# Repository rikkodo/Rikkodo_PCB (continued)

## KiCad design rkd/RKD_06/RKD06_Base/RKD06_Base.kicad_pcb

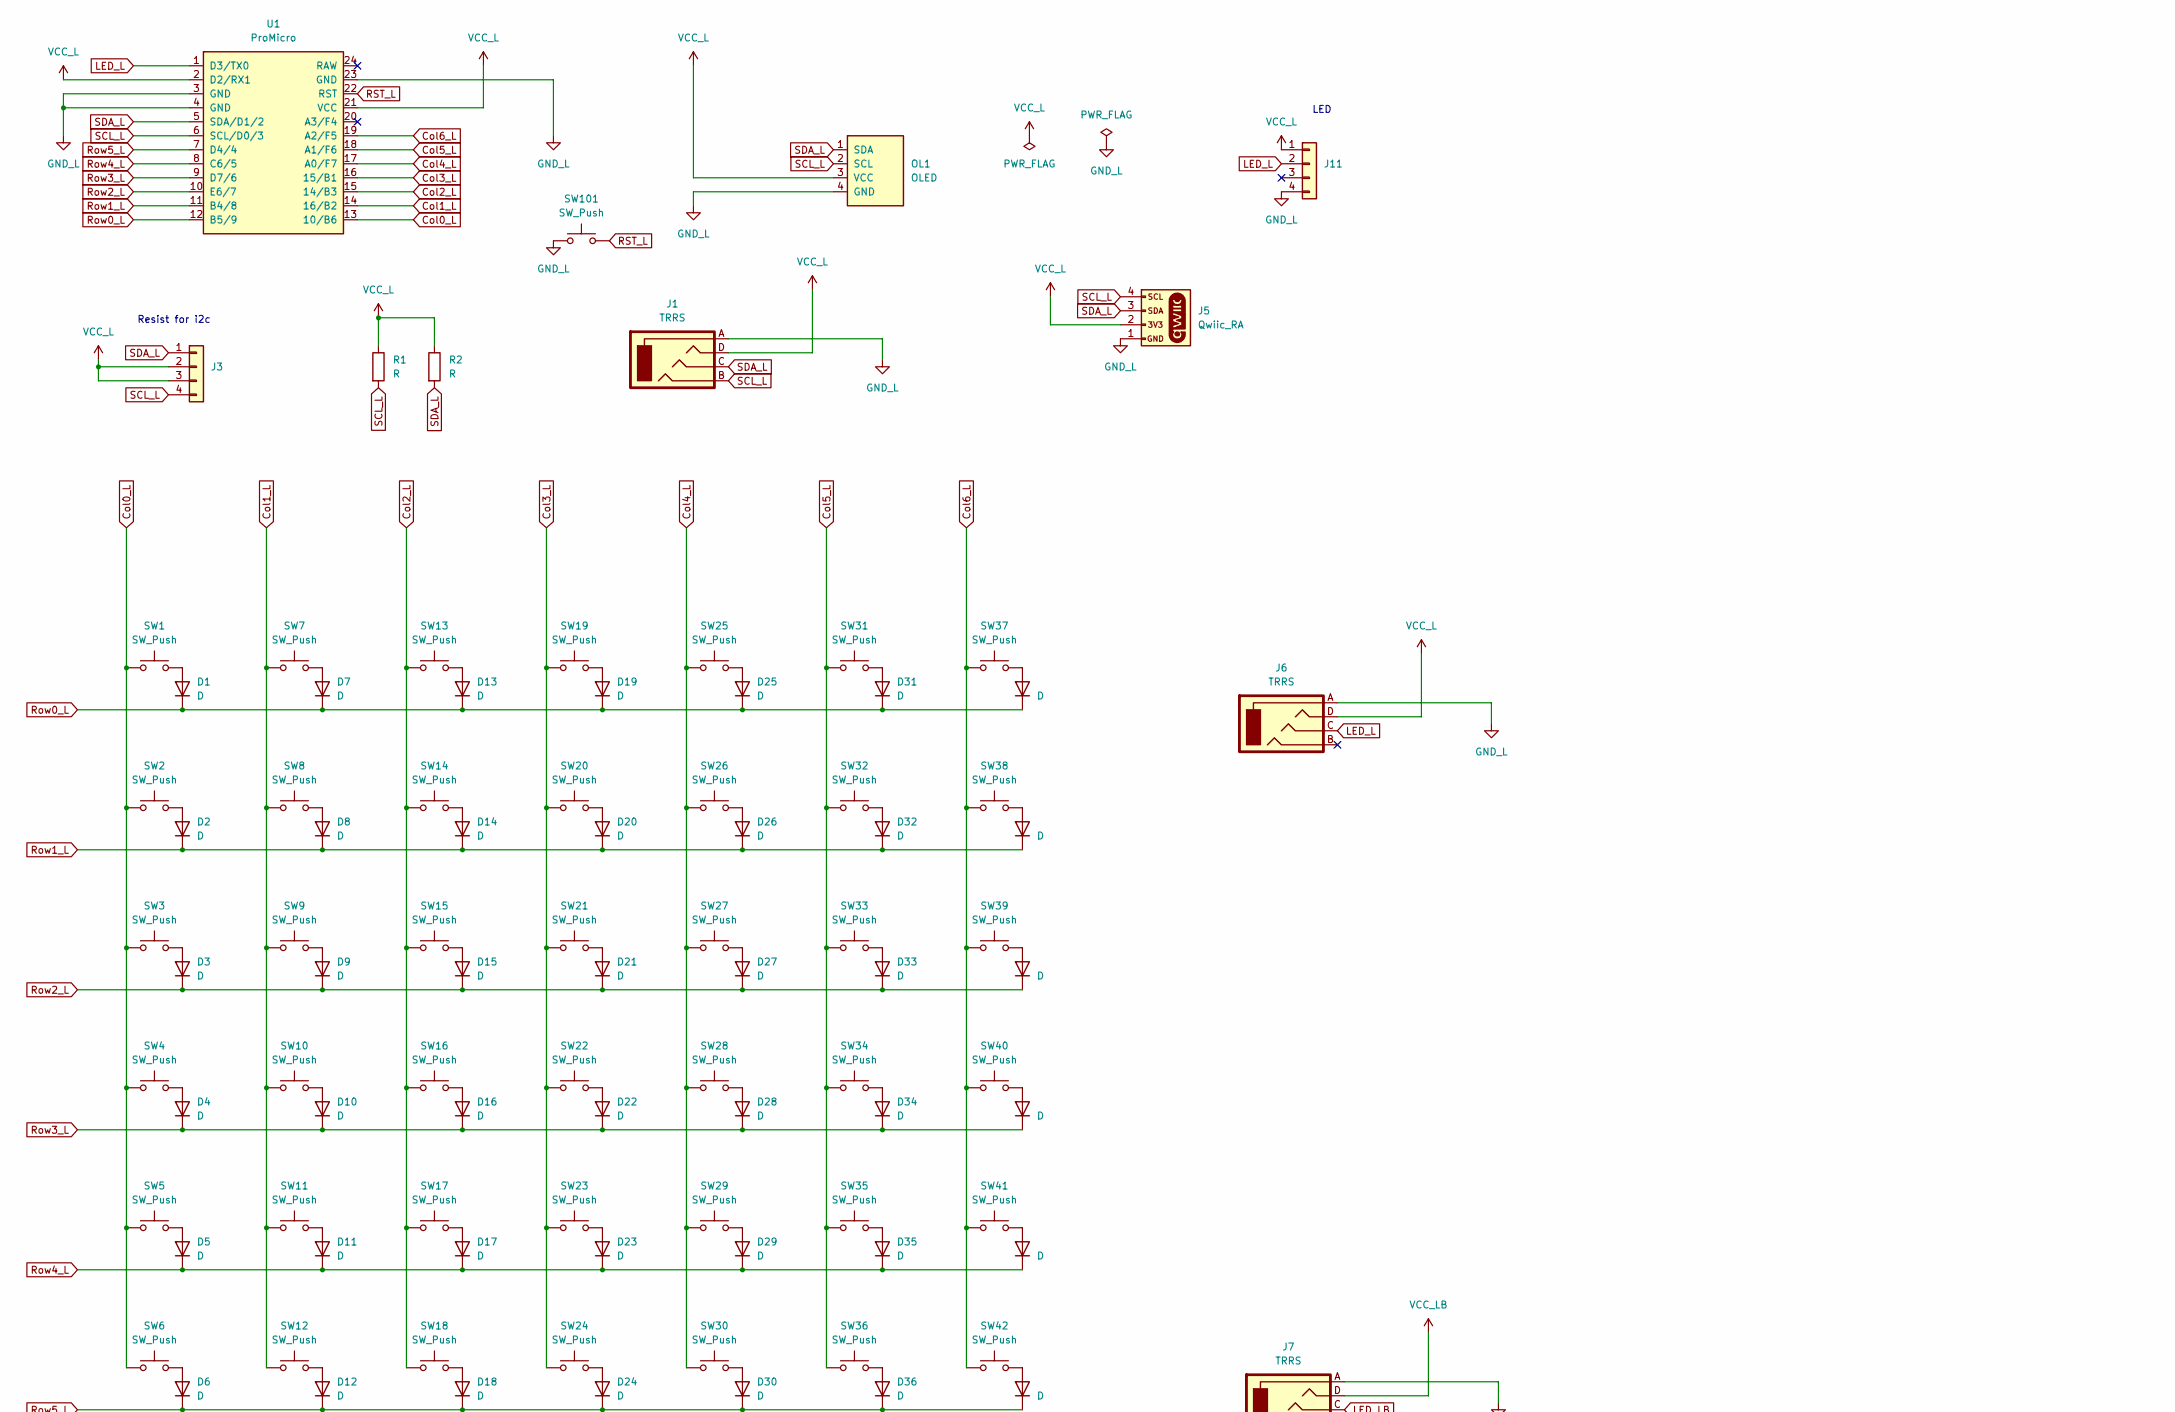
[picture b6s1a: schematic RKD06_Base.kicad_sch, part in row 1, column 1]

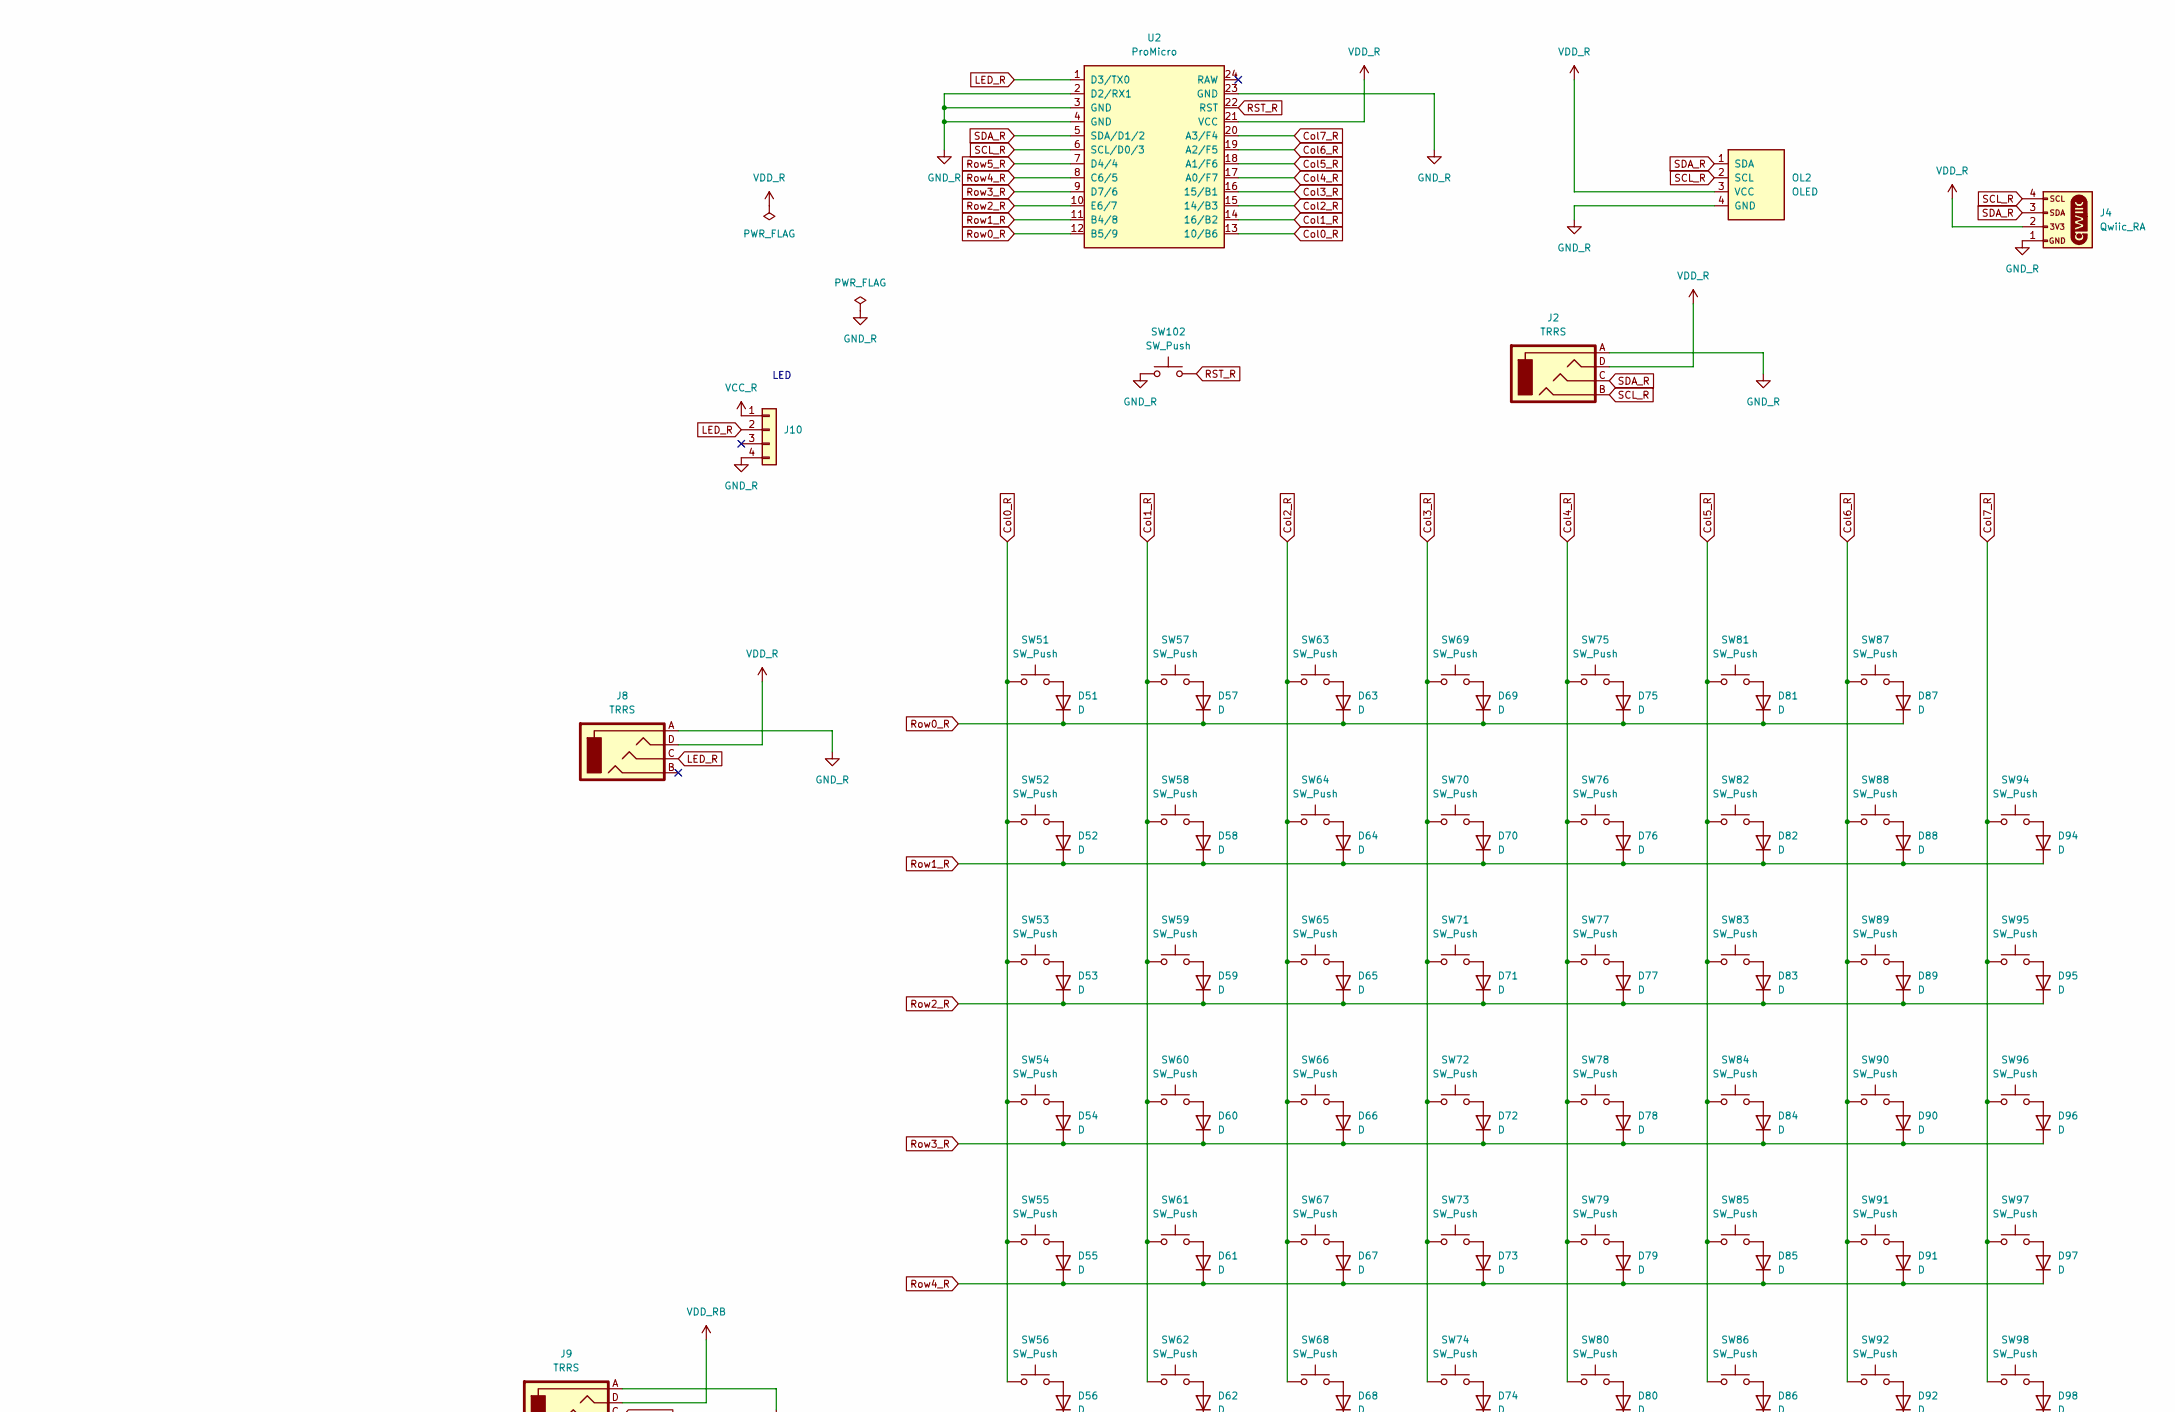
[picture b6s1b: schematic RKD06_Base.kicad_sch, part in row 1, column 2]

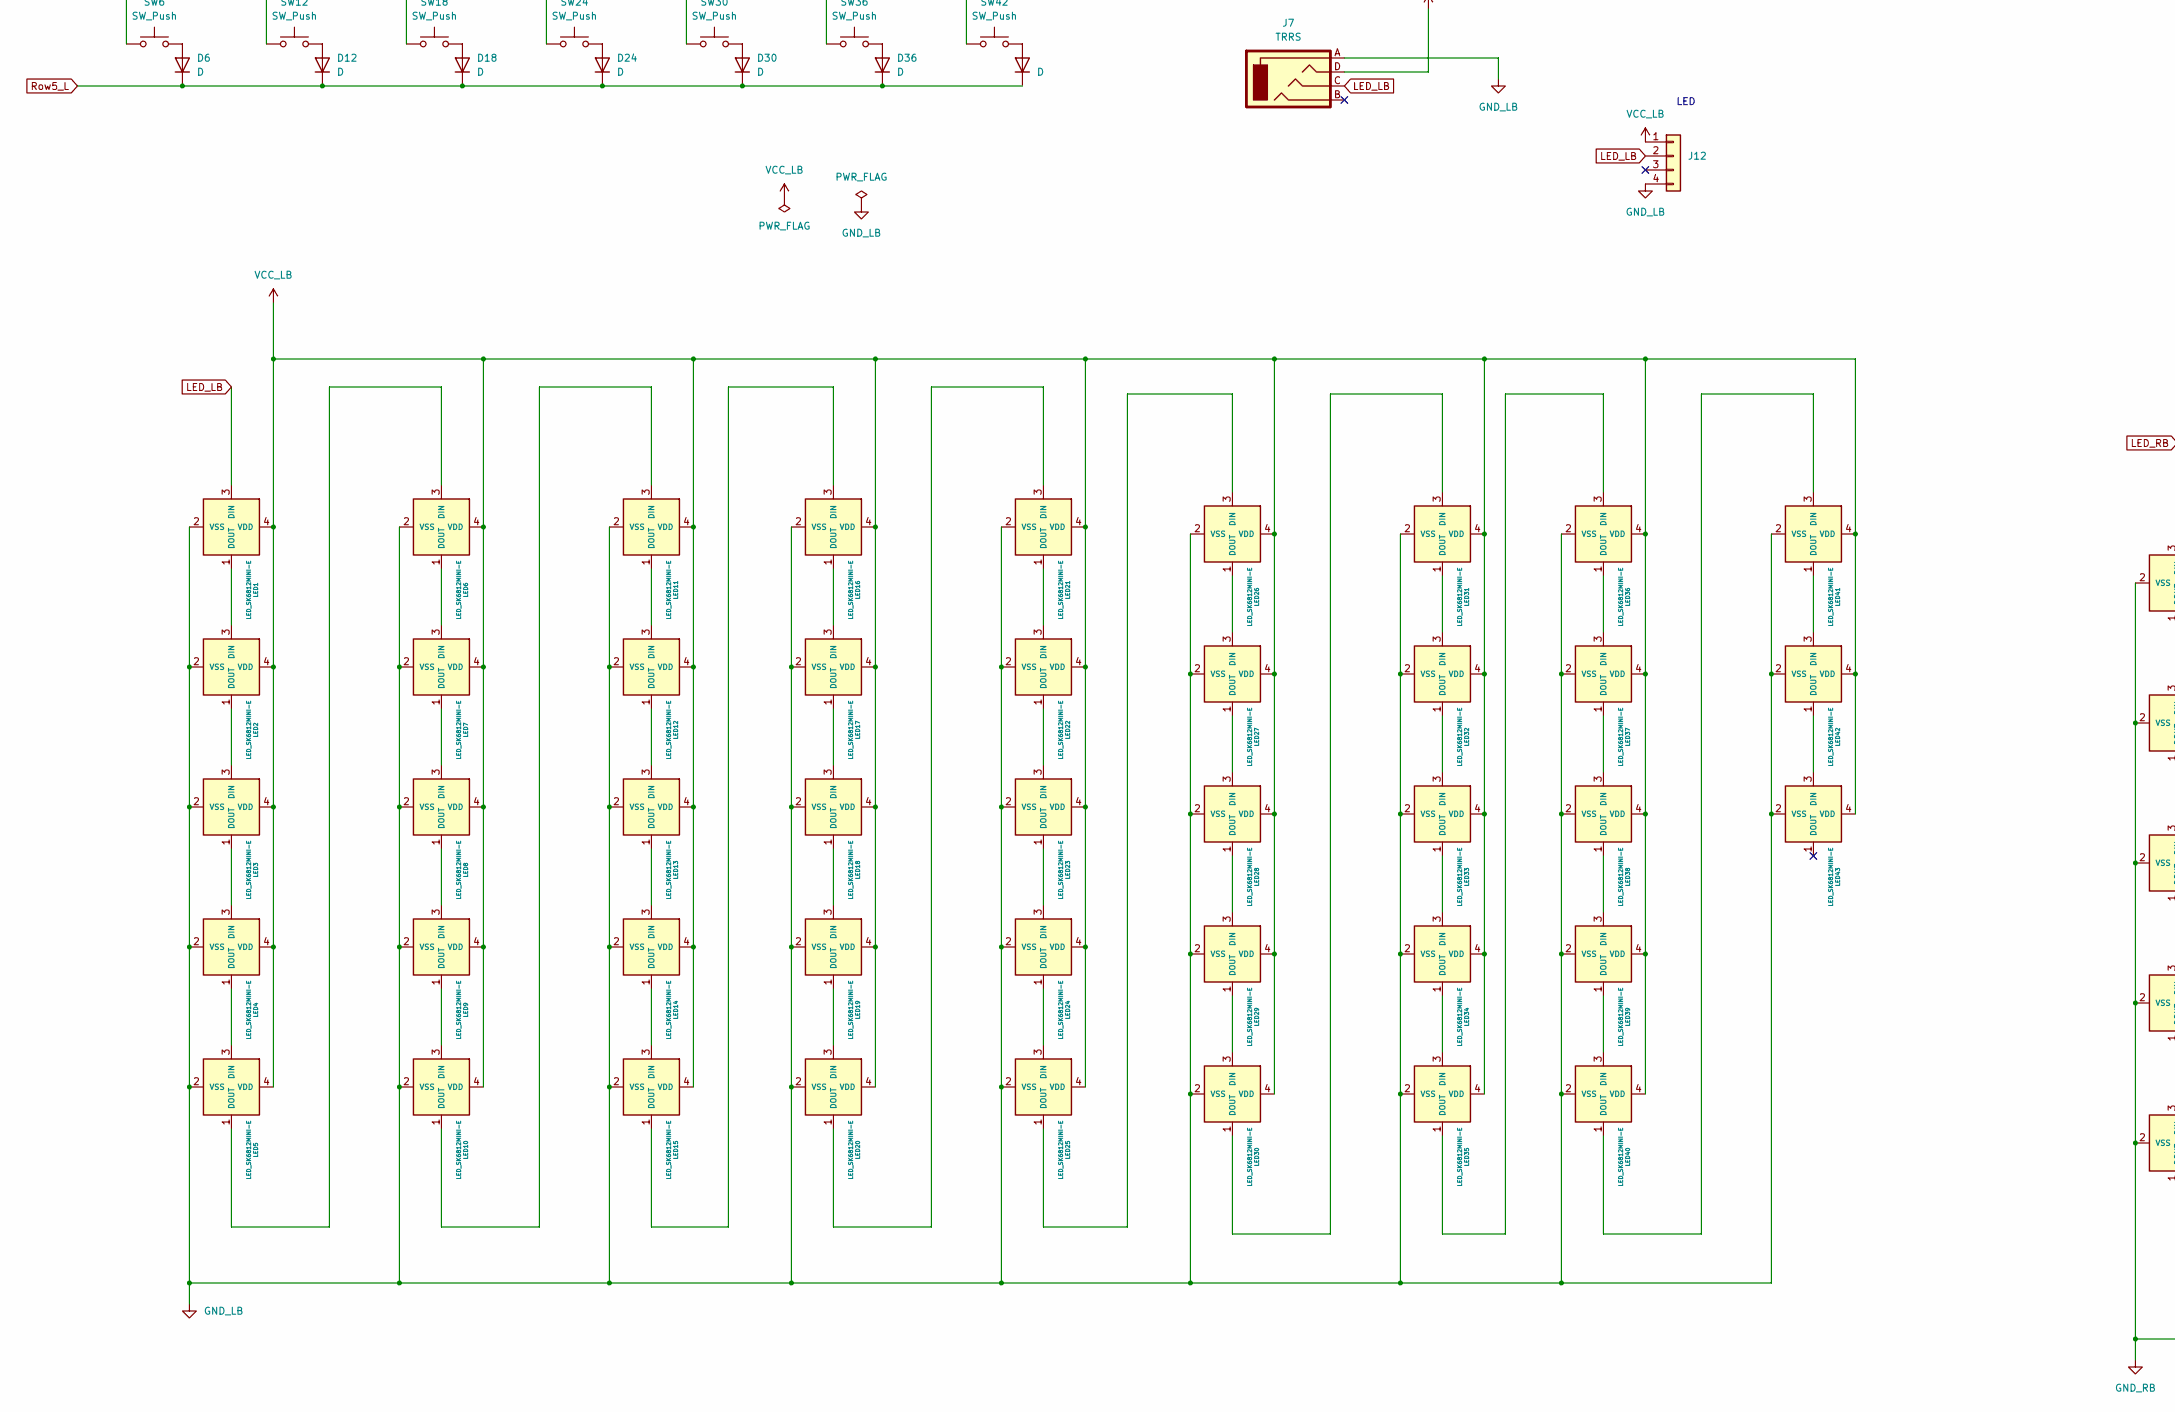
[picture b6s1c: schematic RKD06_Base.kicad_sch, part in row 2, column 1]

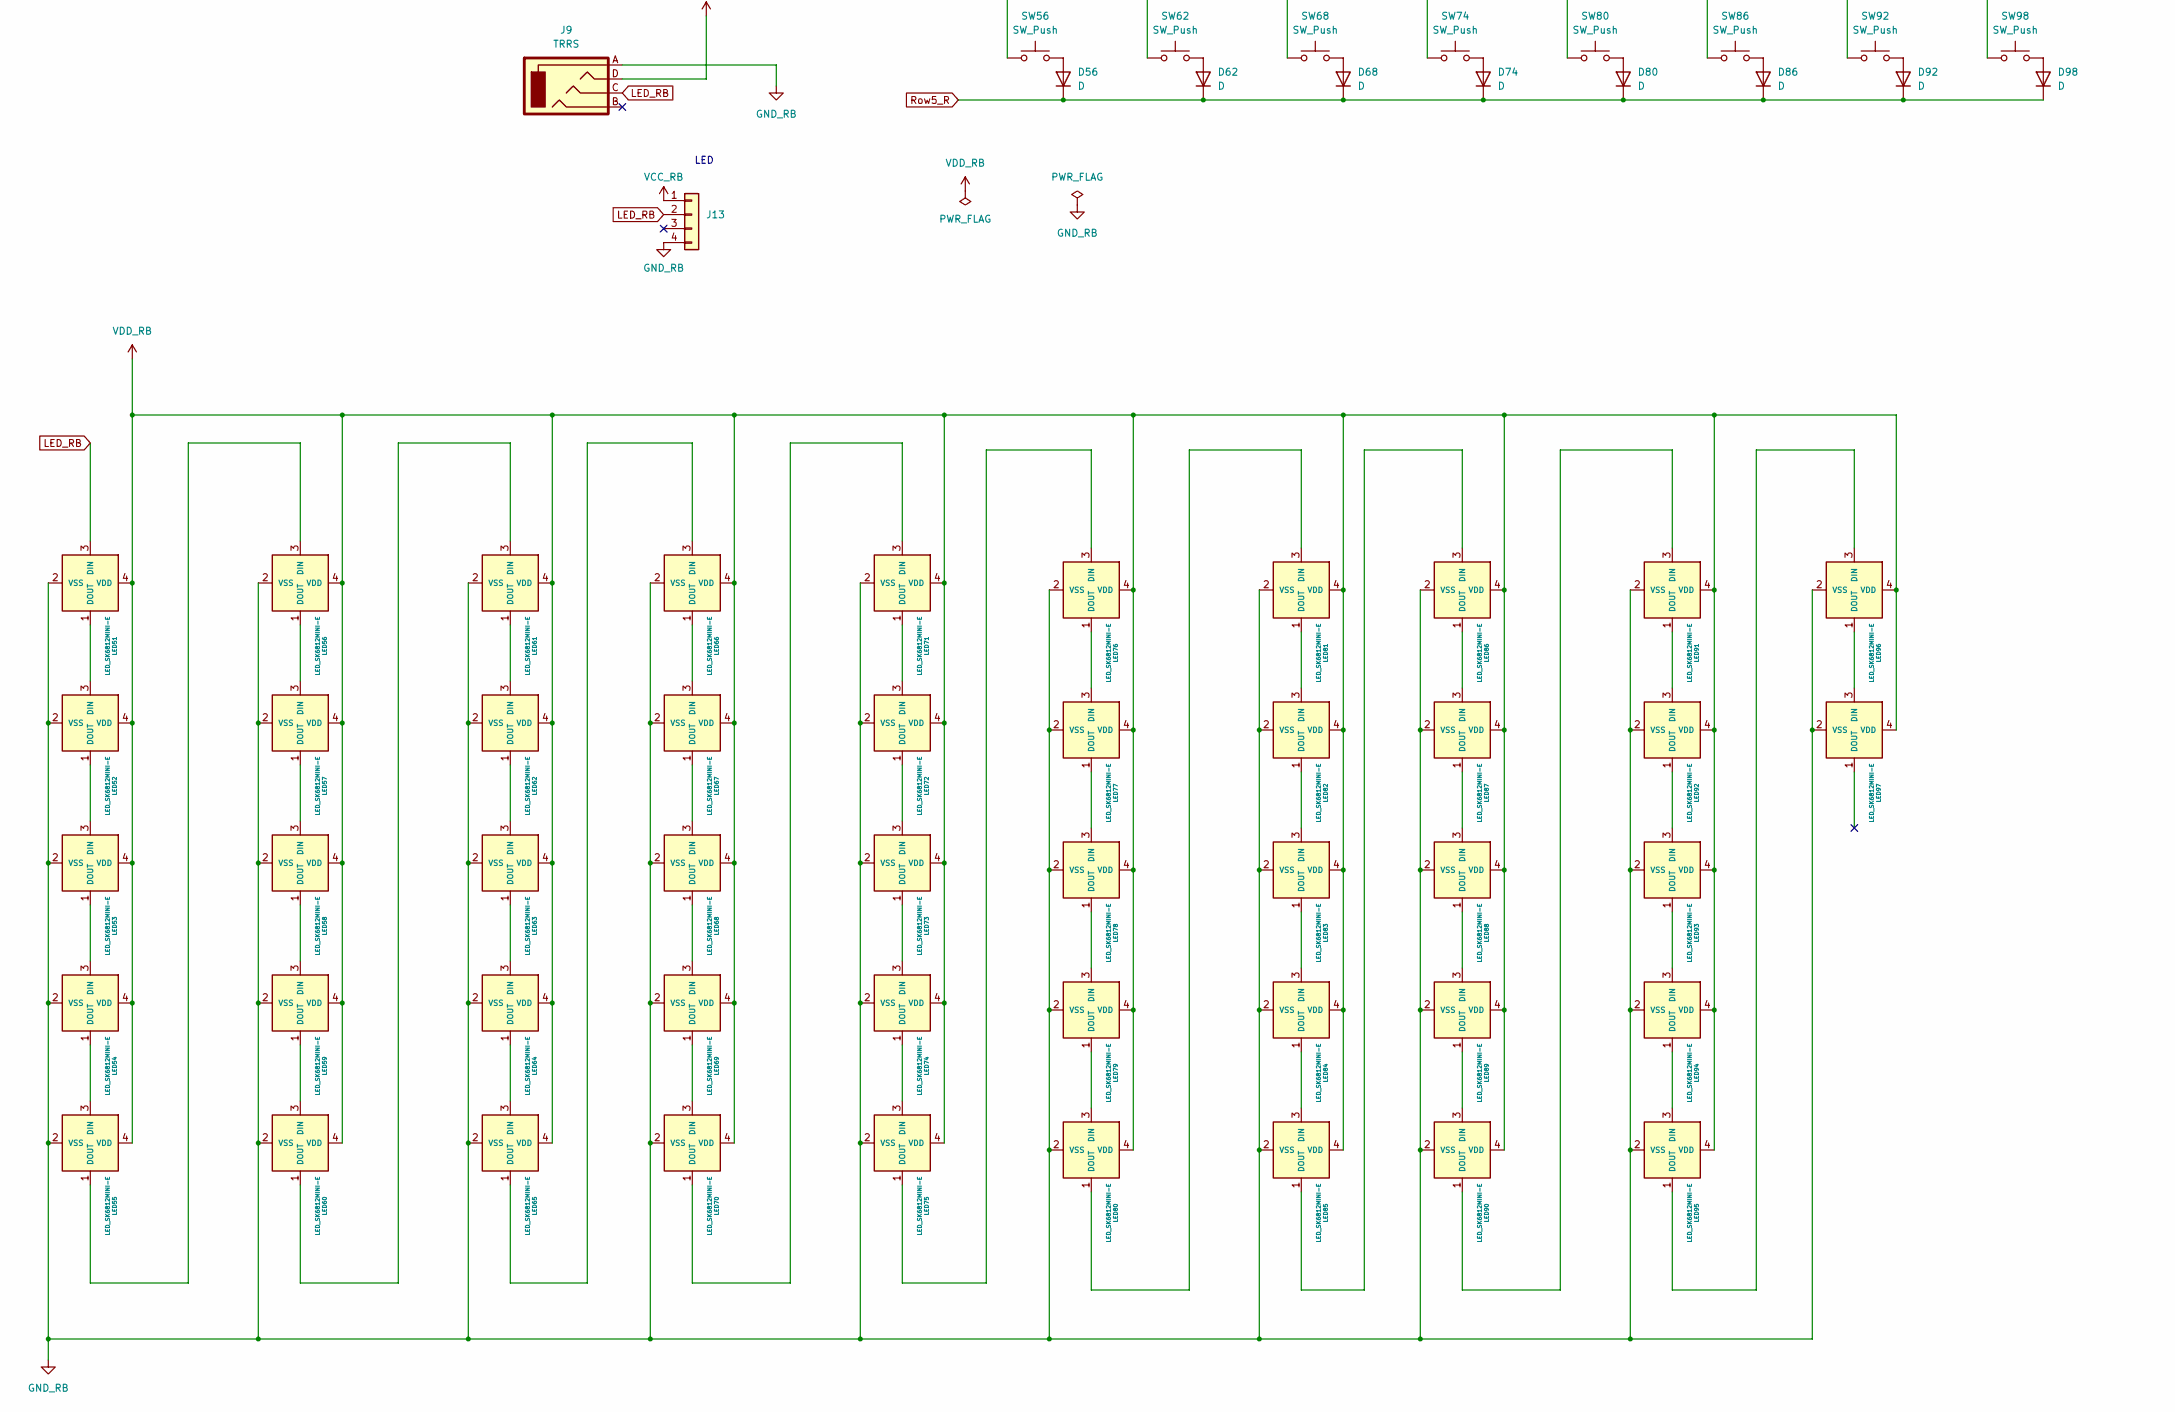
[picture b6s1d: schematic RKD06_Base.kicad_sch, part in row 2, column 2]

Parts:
D1, D2, D3, D4, D5, D6, D7, D8, D9, D10, D11, D12, D13, D14, D15, D16, D17, D18, D19, D20, D21, D22, D23, D24, D25, D26, D27, D28, D29, D30, D31, D32, D33, D34, D35, D36, D37, D38, D39, D40, D41, D42, D51, D52, D53, D54, D55, D56, D57, D58, D59, D60, D61, D62, D63, D64, D65, D66, D67, D68, D69, D70, D71, D72, D73, D74, D75, D76, D77, D78, D79, D80, D81, D82, D83, D84, D85, D86, D87, D88, D89, D90, D91, D92, D94, D95, D96, D97, D98: D; Diode_SMD
J1, J2, J6, J7, J8, J9: TRRS; TRRS_PJ-320A
J3, J10, J11: Conn_01x04; PinSocket_1x04_P2.54mm_Horizontal
J4, J5: Qwiic_RA; JST_SMD_1.0mm-4_Black
J12, J13: Conn_01x04; PinHeader_1x04_P2.54mm_Horizontal
LED1, LED2, LED3, LED4, LED5, LED6, LED7, LED8, LED9, LED10, LED11, LED12, LED13, LED14, LED15, LED16, LED17, LED18, LED19, LED20, LED21, LED22, LED23, LED24, LED25, LED26, LED27, LED28, LED29, LED30, LED31, LED32, LED33, LED34, LED35, LED36, LED37, LED38, LED39, LED40, LED41, LED42, LED43, LED51, LED52, LED53, LED54, LED55, LED56, LED57, LED58, LED59, LED60, LED61, LED62, LED63, LED64, LED65, LED66, LED67, LED68, LED69, LED70, LED71, LED72, LED73, LED74, LED75, LED76, LED77, LED78, LED79, LED80, LED81, LED82, LED83, LED84, LED85, LED86, LED87, LED88, LED89, LED90, LED91, LED92, LED93, LED94, LED95, LED96, LED97: LED_SK6812MINI-E; LED_SK6812MINI-E_BL
OL1, OL2: OLED; OLED_center_module
R1, R2: R; R_Axial_DIN0207_L6.3mm_D2.5mm_P10.16mm_Horizontal
SW1, SW2, SW3, SW4, SW5, SW6, SW7, SW8, SW9, SW10, SW12, SW13, SW14, SW15, SW16, SW17, SW18, SW19, SW20, SW21, SW22, SW23, SW24, SW25, SW26, SW27, SW28, SW29, SW30, SW31, SW32, SW33, SW34, SW35, SW37, SW38, SW39, SW40, SW41, SW42, SW51, SW52, SW53, SW54, SW55, SW56, SW57, SW58, SW59, SW60, SW61, SW62, SW63, SW64, SW65, SW66, SW67, SW68, SW69, SW70, SW71, SW72, SW73, SW74, SW75, SW76, SW77, SW78, SW79, SW80, SW81, SW82, SW83, SW84, SW85, SW86, SW87, SW88, SW89, SW90, SW91, SW92, SW95, SW97, SW98: SW_Push; rkd_Asm_ChocV1V2_Hotswap_1u
SW11, SW36, SW94, SW96: SW_Push; rkd_Asm_ChocV1V2byV1_Hotswap_2u
SW101, SW102: SW_Push; ResetSW
U1, U2: ProMicro; ProMicro_r

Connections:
Col0_L: SW1.2, SW2.2, SW3.2, SW4.2, SW5.2, SW6.2, U1.13 (10/B6)
Col0_R: SW51.2, SW52.2, SW53.2, SW54.2, SW55.2, SW56.2, U2.13 (10/B6)
Col1_L: SW7.2, SW8.2, SW9.2, SW10.2, SW11.2, SW12.2, U1.14 (16/B2)
Col1_R: SW57.2, SW58.2, SW59.2, SW60.2, SW61.2, SW62.2, U2.14 (16/B2)
Col2_L: SW13.2, SW14.2, SW15.2, SW16.2, SW17.2, SW18.2, U1.15 (14/B3)
Col2_R: SW63.2, SW64.2, SW65.2, SW66.2, SW67.2, SW68.2, U2.15 (14/B3)
Col3_L: SW19.2, SW20.2, SW21.2, SW22.2, SW23.2, SW24.2, U1.16 (15/B1)
Col3_R: SW69.2, SW70.2, SW71.2, SW72.2, SW73.2, SW74.2, U2.16 (15/B1)
Col4_L: SW25.2, SW26.2, SW27.2, SW28.2, SW29.2, SW30.2, U1.17 (A0/F7)
Col4_R: SW75.2, SW76.2, SW77.2, SW78.2, SW79.2, SW80.2, U2.17 (A0/F7)
Col5_L: SW31.2, SW32.2, SW33.2, SW34.2, SW35.2, SW36.2, U1.18 (A1/F6)
Col5_R: SW81.2, SW82.2, SW83.2, SW84.2, SW85.2, SW86.2, U2.18 (A1/F6)
Col6_L: SW37.2, SW38.2, SW39.2, SW40.2, SW41.2, SW42.2, U1.19 (A2/F5)
Col6_R: SW87.2, SW88.2, SW89.2, SW90.2, SW91.2, SW92.2, U2.19 (A2/F5)
Col7_R: SW94.2, SW95.2, SW96.2, SW97.2, SW98.2, U2.20 (A3/F4)
GND_L: J1.A, J5.1, J6.A, J11.4, OL1.4 (GND), SW101.2, U1.3 (GND), U1.4 (GND), U1.23 (GND)
GND_LB: J7.A, J12.4, LED1.2 (VSS), LED2.2 (VSS), LED3.2 (VSS), LED4.2 (VSS), LED5.2 (VSS), LED6.2 (VSS), LED7.2 (VSS), LED8.2 (VSS), LED9.2 (VSS), LED10.2 (VSS), LED11.2 (VSS), LED12.2 (VSS), LED13.2 (VSS), LED14.2 (VSS), LED15.2 (VSS), LED16.2 (VSS), LED17.2 (VSS), LED18.2 (VSS), LED19.2 (VSS), LED20.2 (VSS), LED21.2 (VSS), LED22.2 (VSS), LED23.2 (VSS), LED24.2 (VSS), LED25.2 (VSS), LED26.2 (VSS), LED27.2 (VSS), LED28.2 (VSS), LED29.2 (VSS), LED30.2 (VSS), LED31.2 (VSS), LED32.2 (VSS), LED33.2 (VSS), LED34.2 (VSS), LED35.2 (VSS), LED36.2 (VSS), LED37.2 (VSS), LED38.2 (VSS), LED39.2 (VSS), LED40.2 (VSS), LED41.2 (VSS), LED42.2 (VSS), LED43.2 (VSS)
GND_R: J2.A, J4.1, J8.A, J10.4, OL2.4 (GND), SW102.2, U2.2 (D2/RX1), U2.3 (GND), U2.4 (GND), U2.23 (GND)
GND_RB: J9.A, J13.4, LED51.2 (VSS), LED52.2 (VSS), LED53.2 (VSS), LED54.2 (VSS), LED55.2 (VSS), LED56.2 (VSS), LED57.2 (VSS), LED58.2 (VSS), LED59.2 (VSS), LED60.2 (VSS), LED61.2 (VSS), LED62.2 (VSS), LED63.2 (VSS), LED64.2 (VSS), LED65.2 (VSS), LED66.2 (VSS), LED67.2 (VSS), LED68.2 (VSS), LED69.2 (VSS), LED70.2 (VSS), LED71.2 (VSS), LED72.2 (VSS), LED73.2 (VSS), LED74.2 (VSS), LED75.2 (VSS), LED76.2 (VSS), LED77.2 (VSS), LED78.2 (VSS), LED79.2 (VSS), LED80.2 (VSS), LED81.2 (VSS), LED82.2 (VSS), LED83.2 (VSS), LED84.2 (VSS), LED85.2 (VSS), LED86.2 (VSS), LED87.2 (VSS), LED88.2 (VSS), LED89.2 (VSS), LED90.2 (VSS), LED91.2 (VSS), LED92.2 (VSS), LED93.2 (VSS), LED94.2 (VSS), LED95.2 (VSS), LED96.2 (VSS), LED97.2 (VSS)
LED_L: J6.C, J11.2, U1.1 (D3/TX0)
LED_LB: J7.C, J12.2, LED1.3 (DIN)
LED_R: J8.C, J10.2, U2.1 (D3/TX0)
LED_RB: J9.C, J13.2, LED51.3 (DIN)
unnamed: D1.2 (A), SW1.1
unnamed: D2.2 (A), SW2.1
unnamed: D3.2 (A), SW3.1
unnamed: D4.2 (A), SW4.1
unnamed: D5.2 (A), SW5.1
unnamed: D6.2 (A), SW6.1
unnamed: D7.2 (A), SW7.1
unnamed: D8.2 (A), SW8.1
unnamed: D9.2 (A), SW9.1
unnamed: D10.2 (A), SW10.1
unnamed: D11.2 (A), SW11.1
unnamed: D12.2 (A), SW12.1
unnamed: D13.2 (A), SW13.1
unnamed: D14.2 (A), SW14.1
unnamed: D15.2 (A), SW15.1
unnamed: D16.2 (A), SW16.1
unnamed: D17.2 (A), SW17.1
unnamed: D18.2 (A), SW18.1
unnamed: D19.2 (A), SW19.1
unnamed: D20.2 (A), SW20.1
unnamed: D21.2 (A), SW21.1
unnamed: D22.2 (A), SW22.1
unnamed: D23.2 (A), SW23.1
unnamed: D24.2 (A), SW24.1
unnamed: D25.2 (A), SW25.1
unnamed: D26.2 (A), SW26.1
unnamed: D27.2 (A), SW27.1
unnamed: D28.2 (A), SW28.1
unnamed: D29.2 (A), SW29.1
unnamed: D30.2 (A), SW30.1
unnamed: D31.2 (A), SW31.1
unnamed: D32.2 (A), SW32.1
unnamed: D33.2 (A), SW33.1
unnamed: D34.2 (A), SW34.1
unnamed: D35.2 (A), SW35.1
unnamed: D36.2 (A), SW36.1
unnamed: D37.2 (A), SW37.1
unnamed: D38.2 (A), SW38.1
unnamed: D39.2 (A), SW39.1
unnamed: D40.2 (A), SW40.1
unnamed: D41.2 (A), SW41.1
unnamed: D42.2 (A), SW42.1
unnamed: D51.2 (A), SW51.1
unnamed: D52.2 (A), SW52.1
unnamed: D53.2 (A), SW53.1
unnamed: D54.2 (A), SW54.1
unnamed: D55.2 (A), SW55.1
unnamed: D56.2 (A), SW56.1
unnamed: D57.2 (A), SW57.1
unnamed: D58.2 (A), SW58.1
unnamed: D59.2 (A), SW59.1
unnamed: D60.2 (A), SW60.1
unnamed: D61.2 (A), SW61.1
unnamed: D62.2 (A), SW62.1
unnamed: D63.2 (A), SW63.1
unnamed: D64.2 (A), SW64.1
unnamed: D65.2 (A), SW65.1
unnamed: D66.2 (A), SW66.1
unnamed: D67.2 (A), SW67.1
unnamed: D68.2 (A), SW68.1
unnamed: D69.2 (A), SW69.1
unnamed: D70.2 (A), SW70.1
unnamed: D71.2 (A), SW71.1
unnamed: D72.2 (A), SW72.1
unnamed: D73.2 (A), SW73.1
unnamed: D74.2 (A), SW74.1
unnamed: D75.2 (A), SW75.1
unnamed: D76.2 (A), SW76.1
unnamed: D77.2 (A), SW77.1
unnamed: D78.2 (A), SW78.1
unnamed: D79.2 (A), SW79.1
unnamed: D80.2 (A), SW80.1
unnamed: D81.2 (A), SW81.1
unnamed: D82.2 (A), SW82.1
unnamed: D83.2 (A), SW83.1
unnamed: D84.2 (A), SW84.1
unnamed: D85.2 (A), SW85.1
unnamed: D86.2 (A), SW86.1
unnamed: D87.2 (A), SW87.1
unnamed: D88.2 (A), SW88.1
unnamed: D89.2 (A), SW89.1
unnamed: D90.2 (A), SW90.1
unnamed: D91.2 (A), SW91.1
unnamed: D92.2 (A), SW92.1
unnamed: D94.2 (A), SW94.1
unnamed: D95.2 (A), SW95.1
unnamed: D96.2 (A), SW96.1
unnamed: D97.2 (A), SW97.1
unnamed: D98.2 (A), SW98.1
unnamed: LED1.1 (DOUT), LED2.3 (DIN)
unnamed: LED2.1 (DOUT), LED3.3 (DIN)
unnamed: LED3.1 (DOUT), LED4.3 (DIN)
unnamed: LED4.1 (DOUT), LED5.3 (DIN)
unnamed: LED5.1 (DOUT), LED6.3 (DIN)
unnamed: LED6.1 (DOUT), LED7.3 (DIN)
unnamed: LED7.1 (DOUT), LED8.3 (DIN)
unnamed: LED8.1 (DOUT), LED9.3 (DIN)
unnamed: LED9.1 (DOUT), LED10.3 (DIN)
unnamed: LED10.1 (DOUT), LED11.3 (DIN)
unnamed: LED11.1 (DOUT), LED12.3 (DIN)
unnamed: LED12.1 (DOUT), LED13.3 (DIN)
unnamed: LED13.1 (DOUT), LED14.3 (DIN)
unnamed: LED14.1 (DOUT), LED15.3 (DIN)
unnamed: LED15.1 (DOUT), LED16.3 (DIN)
unnamed: LED16.1 (DOUT), LED17.3 (DIN)
unnamed: LED17.1 (DOUT), LED18.3 (DIN)
unnamed: LED18.1 (DOUT), LED19.3 (DIN)
unnamed: LED19.1 (DOUT), LED20.3 (DIN)
unnamed: LED20.1 (DOUT), LED21.3 (DIN)
unnamed: LED21.1 (DOUT), LED22.3 (DIN)
unnamed: LED22.1 (DOUT), LED23.3 (DIN)
unnamed: LED23.1 (DOUT), LED24.3 (DIN)
unnamed: LED24.1 (DOUT), LED25.3 (DIN)
unnamed: LED25.1 (DOUT), LED26.3 (DIN)
unnamed: LED26.1 (DOUT), LED27.3 (DIN)
unnamed: LED27.1 (DOUT), LED28.3 (DIN)
unnamed: LED28.1 (DOUT), LED29.3 (DIN)
unnamed: LED29.1 (DOUT), LED30.3 (DIN)
unnamed: LED30.1 (DOUT), LED31.3 (DIN)
unnamed: LED31.1 (DOUT), LED32.3 (DIN)
unnamed: LED32.1 (DOUT), LED33.3 (DIN)
unnamed: LED33.1 (DOUT), LED34.3 (DIN)
unnamed: LED34.1 (DOUT), LED35.3 (DIN)
unnamed: LED35.1 (DOUT), LED36.3 (DIN)
unnamed: LED36.1 (DOUT), LED37.3 (DIN)
unnamed: LED37.1 (DOUT), LED38.3 (DIN)
unnamed: LED38.1 (DOUT), LED39.3 (DIN)
unnamed: LED39.1 (DOUT), LED40.3 (DIN)
unnamed: LED40.1 (DOUT), LED41.3 (DIN)
unnamed: LED41.1 (DOUT), LED42.3 (DIN)
unnamed: LED42.1 (DOUT), LED43.3 (DIN)
unnamed: LED51.1 (DOUT), LED52.3 (DIN)
unnamed: LED52.1 (DOUT), LED53.3 (DIN)
unnamed: LED53.1 (DOUT), LED54.3 (DIN)
unnamed: LED54.1 (DOUT), LED55.3 (DIN)
unnamed: LED55.1 (DOUT), LED56.3 (DIN)
unnamed: LED56.1 (DOUT), LED57.3 (DIN)
unnamed: LED57.1 (DOUT), LED58.3 (DIN)
unnamed: LED58.1 (DOUT), LED59.3 (DIN)
unnamed: LED59.1 (DOUT), LED60.3 (DIN)
unnamed: LED60.1 (DOUT), LED61.3 (DIN)
unnamed: LED61.1 (DOUT), LED62.3 (DIN)
unnamed: LED62.1 (DOUT), LED63.3 (DIN)
unnamed: LED63.1 (DOUT), LED64.3 (DIN)
unnamed: LED64.1 (DOUT), LED65.3 (DIN)
unnamed: LED65.1 (DOUT), LED66.3 (DIN)
unnamed: LED66.1 (DOUT), LED67.3 (DIN)
unnamed: LED67.1 (DOUT), LED68.3 (DIN)
unnamed: LED68.1 (DOUT), LED69.3 (DIN)
unnamed: LED69.1 (DOUT), LED70.3 (DIN)
unnamed: LED70.1 (DOUT), LED71.3 (DIN)
unnamed: LED71.1 (DOUT), LED72.3 (DIN)
unnamed: LED72.1 (DOUT), LED73.3 (DIN)
unnamed: LED73.1 (DOUT), LED74.3 (DIN)
unnamed: LED74.1 (DOUT), LED75.3 (DIN)
unnamed: LED75.1 (DOUT), LED76.3 (DIN)
unnamed: LED76.1 (DOUT), LED77.3 (DIN)
unnamed: LED77.1 (DOUT), LED78.3 (DIN)
unnamed: LED78.1 (DOUT), LED79.3 (DIN)
unnamed: LED79.1 (DOUT), LED80.3 (DIN)
unnamed: LED80.1 (DOUT), LED81.3 (DIN)
unnamed: LED81.1 (DOUT), LED82.3 (DIN)
unnamed: LED82.1 (DOUT), LED83.3 (DIN)
unnamed: LED83.1 (DOUT), LED84.3 (DIN)
unnamed: LED84.1 (DOUT), LED85.3 (DIN)
unnamed: LED85.1 (DOUT), LED86.3 (DIN)
unnamed: LED86.1 (DOUT), LED87.3 (DIN)
unnamed: LED87.1 (DOUT), LED88.3 (DIN)
unnamed: LED88.1 (DOUT), LED89.3 (DIN)
unnamed: LED89.1 (DOUT), LED90.3 (DIN)
unnamed: LED90.1 (DOUT), LED91.3 (DIN)
unnamed: LED91.1 (DOUT), LED92.3 (DIN)
unnamed: LED92.1 (DOUT), LED93.3 (DIN)
unnamed: LED93.1 (DOUT), LED94.3 (DIN)
unnamed: LED94.1 (DOUT), LED95.3 (DIN)
unnamed: LED95.1 (DOUT), LED96.3 (DIN)
unnamed: LED96.1 (DOUT), LED97.3 (DIN)
RST_L: SW101.1, U1.22 (RST)
RST_R: SW102.1, U2.22 (RST)
Row0_L: D1.1 (K), D7.1 (K), D13.1 (K), D19.1 (K), D25.1 (K), D31.1 (K), D37.1 (K), U1.12 (B5/9)
Row0_R: D51.1 (K), D57.1 (K), D63.1 (K), D69.1 (K), D75.1 (K), D81.1 (K), D87.1 (K), U2.12 (B5/9)
Row1_L: D2.1 (K), D8.1 (K), D14.1 (K), D20.1 (K), D26.1 (K), D32.1 (K), D38.1 (K), U1.11 (B4/8)
Row1_R: D52.1 (K), D58.1 (K), D64.1 (K), D70.1 (K), D76.1 (K), D82.1 (K), D88.1 (K), D94.1 (K), U2.11 (B4/8)
Row2_L: D3.1 (K), D9.1 (K), D15.1 (K), D21.1 (K), D27.1 (K), D33.1 (K), D39.1 (K), U1.10 (E6/7)
Row2_R: D53.1 (K), D59.1 (K), D65.1 (K), D71.1 (K), D77.1 (K), D83.1 (K), D89.1 (K), D95.1 (K), U2.10 (E6/7)
Row3_L: D4.1 (K), D10.1 (K), D16.1 (K), D22.1 (K), D28.1 (K), D34.1 (K), D40.1 (K), U1.9 (D7/6)
Row3_R: D54.1 (K), D60.1 (K), D66.1 (K), D72.1 (K), D78.1 (K), D84.1 (K), D90.1 (K), D96.1 (K), U2.9 (D7/6)
Row4_L: D5.1 (K), D11.1 (K), D17.1 (K), D23.1 (K), D29.1 (K), D35.1 (K), D41.1 (K), U1.8 (C6/5)
Row4_R: D55.1 (K), D61.1 (K), D67.1 (K), D73.1 (K), D79.1 (K), D85.1 (K), D91.1 (K), D97.1 (K), U2.8 (C6/5)
Row5_L: D6.1 (K), D12.1 (K), D18.1 (K), D24.1 (K), D30.1 (K), D36.1 (K), D42.1 (K), U1.7 (D4/4)
Row5_R: D56.1 (K), D62.1 (K), D68.1 (K), D74.1 (K), D80.1 (K), D86.1 (K), D92.1 (K), D98.1 (K), U2.7 (D4/4)
SCL_L: J1.B, J3.4, J5.4, OL1.2 (SCL), R1.2, U1.6 (SCL/D0/3)
SCL_R: J2.B, J4.4, OL2.2 (SCL), U2.6 (SCL/D0/3)
SDA_L: J1.C, J3.1, J5.3, OL1.1 (SDA), R2.2, U1.5 (SDA/D1/2)
SDA_R: J2.C, J4.3, OL2.1 (SDA), U2.5 (SDA/D1/2)
VCC_L: J1.D, J3.2, J3.3, J5.2, J6.D, J11.1, OL1.3 (VCC), R1.1, R2.1, U1.2 (D2/RX1), U1.21 (VCC)
VCC_LB: J7.D, J12.1, LED1.4 (VDD), LED2.4 (VDD), LED3.4 (VDD), LED4.4 (VDD), LED5.4 (VDD), LED6.4 (VDD), LED7.4 (VDD), LED8.4 (VDD), LED9.4 (VDD), LED10.4 (VDD), LED11.4 (VDD), LED12.4 (VDD), LED13.4 (VDD), LED14.4 (VDD), LED15.4 (VDD), LED16.4 (VDD), LED17.4 (VDD), LED18.4 (VDD), LED19.4 (VDD), LED20.4 (VDD), LED21.4 (VDD), LED22.4 (VDD), LED23.4 (VDD), LED24.4 (VDD), LED25.4 (VDD), LED26.4 (VDD), LED27.4 (VDD), LED28.4 (VDD), LED29.4 (VDD), LED30.4 (VDD), LED31.4 (VDD), LED32.4 (VDD), LED33.4 (VDD), LED34.4 (VDD), LED35.4 (VDD), LED36.4 (VDD), LED37.4 (VDD), LED38.4 (VDD), LED39.4 (VDD), LED40.4 (VDD), LED41.4 (VDD), LED42.4 (VDD), LED43.4 (VDD)
VCC_R: J10.1
VCC_RB: J13.1
VDD_R: J2.D, J4.2, J8.D, OL2.3 (VCC), U2.21 (VCC)
VDD_RB: J9.D, LED51.4 (VDD), LED52.4 (VDD), LED53.4 (VDD), LED54.4 (VDD), LED55.4 (VDD), LED56.4 (VDD), LED57.4 (VDD), LED58.4 (VDD), LED59.4 (VDD), LED60.4 (VDD), LED61.4 (VDD), LED62.4 (VDD), LED63.4 (VDD), LED64.4 (VDD), LED65.4 (VDD), LED66.4 (VDD), LED67.4 (VDD), LED68.4 (VDD), LED69.4 (VDD), LED70.4 (VDD), LED71.4 (VDD), LED72.4 (VDD), LED73.4 (VDD), LED74.4 (VDD), LED75.4 (VDD), LED76.4 (VDD), LED77.4 (VDD), LED78.4 (VDD), LED79.4 (VDD), LED80.4 (VDD), LED81.4 (VDD), LED82.4 (VDD), LED83.4 (VDD), LED84.4 (VDD), LED85.4 (VDD), LED86.4 (VDD), LED87.4 (VDD), LED88.4 (VDD), LED89.4 (VDD), LED90.4 (VDD), LED91.4 (VDD), LED92.4 (VDD), LED93.4 (VDD), LED94.4 (VDD), LED95.4 (VDD), LED96.4 (VDD), LED97.4 (VDD)

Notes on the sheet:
LED
Resist for i2c

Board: 2 copper layers, 299 parts (13 on the bottom side), 222 nets, no tracks yet.

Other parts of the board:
Ref**: Val**; m2_Spacer_Hole_hex
Ref**#2, Ref**#3, Ref**#4, Ref**#5, Ref**#6, Ref**#7, Ref**#8, Ref**#9, Ref**#10: Val**; m2_Spacer_Hole_hex
